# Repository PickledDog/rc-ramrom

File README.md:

# rc-ramrom
 Pageable RAM/ROM card for RC2014

## Overview
This RC2014-compatible board provides both ROM and RAM in a single card. ROM comes from an EPROM or EEPROM, with 8k/16k/32k granularity, and RAM is provided by a 128k x 8 SRAM. The ROM can be paged out and replaced by RAM.

## Memory details
For ROM, multiple EPROM and EEPROM chips are supported (8K through 64K from the 27Cxx and 28Cxx series - see below for supported chips). Room is provided for a ZIF socket for the EPROM, if desired. For RAM, an AS6C1008 SRAM is used, providing 128K of addressable memory. The upper 64K is difficult to use (page size is the entire 64K Z80 address space), but is there for the adventurous coder; consider this 64K of RAM for most purposes.

## Paging
The ROM is enabled by default, appearing at the bottom of memory (the RAM filling the rest of the address space). A config register allows it to be disabled (paged out) and replaced with RAM - this is required by systems like CP/M. A second config register selects between lower and upper 64K RAM banks. These registers are presented as two I/O devices to the system: ROM paging at 0x38, and RAM selection at 0x30. Writing a **1** to 0x38 disables the ROM, and writing a **1** to 0x30 switches to the upper RAM bank. Both of these actions are indicated by LEDs.

The ports are chosen to have the same organization as the [SC114 Motherboard](https://smallcomputercentral.wordpress.com/sc114-documentation/), and the ROM control address is common to most Z80 retrocomputers (the official RC2014 RAM/ROM cards included). As such, this board is basically the SC114's memory subsystem, in card form, with the addition of selectable page size and address.

## Chip support
The board supports 27C64, 27C128, 27C256, and 27C512 EPROMs, as well as 28C64 and 28C256 EEPROMs. Other chips with similar pinouts will *probably* work, but are untested. 150ns parts (like most 28C256s) are running at the edge of their specification in a standard 7.3Mhz system, and may require lowering the CPU clock. The [27C256](https://www.mouser.com/ProductDetail/AT27C256R-70PU/), [27C512](https://www.mouser.com/ProductDetail/AT27C512R-70PU/), and [28C256](https://www.mouser.com/ProductDetail/AT28C256-15PU/) can be purchased new.

## Firmware
Most (if not all) [RC2014 ROM images](https://github.com/RC2014Z80/RC2014/tree/master/ROMs) can be used unmodified (selecting the right images for your serial board, of course). Stephen C Cousins' excellent [Small Computer Monitor](https://smallcomputercentral.wordpress.com/small-computer-monitor/) can be used as well - all of the R\* configurations are supported. You will need an EPROM programmer (for example, a [TL866](https://www.ebay.com/sch/i.html?_nkw=tl866ii+plus)) to load the ROM images onto a chip.

## Jumper settings
Refer to the front and back of the board for detailed jumper setting instructions.

## Part selection
Bill Of Materials and part references are below. I recommend using gold-plated header for the bus connection - I use these ones from [Pololu](https://www.pololu.com/product/967) or [Sparkfun](https://www.sparkfun.com/products/553). A nice detail of these, is that they sit at the same height as double-row header in a backplane. The jumper headers can be snapped from regular (or double-row) breakaway header, for which eBay is substantially cheaper; the Mouser listings are provided for convenience.

The specified parts are just the ones I used, and can be substituted as needed - Mouser links provided for convenience and reference. A ZIF socket can be used for the EPROM - these are best [sourced from eBay](https://www.ebay.com/sch/i.html?_nkw=28+pin+zif+socket).

| Reference | Value | Qty | Mouser link |
| --------- | ----- | --- | ----------- |
| C1-C5 | 100nF ceramic | 5 | [KEMET C315C104M5U5TA](https://www.mouser.com/ProductDetail/C315C104M5U5TA7303) |
| D1, D2 | 3mm green LED | 2 | [Lite-On LTL-4231N](https://www.mouser.com/ProductDetail/LTL-4231N) |
| J1 | 1x40 right-angle header | 1 | [Wurth 61304011021](https://www.mouser.com/ProductDetail/61304011021) |
| JP1/2 | 2x3 header | 1 | [Amphenol 10129381-906002BLF](https://www.mouser.com/ProductDetail/10129381-906002BLF) |
| JP3/4/5 | 3x3 header | 1 | [Samtec TSW-103-07-L-T](https://www.mouser.com/ProductDetail/TSW-103-07-L-T) |
| JP6 | 2x2 header | 1 | [Amphenol 10129381-904002BLF](https://www.mouser.com/ProductDetail/10129381-904002BLF) |
| | jumpers | 7 | [Harwin M7583-46](https://www.mouser.com/ProductDetail/M7583-46)
| R1, R2 | 470Ω resistor | 2 | [Yageo CFR-25JT-52-470R](https://www.mouser.com/ProductDetail/CFR-25JT-52-470R) |
| R3, R4 | 10kΩ resistor | 2 | [Yageo CFR-25JT-52-10K](https://www.mouser.com/ProductDetail/CFR-25JT-52-10K) |
| U1 | EPROM | 1 | (see above for EPROM choices) |
| | socket | 1 | [Amphenol DILB28P-223TLF](https://www.mouser.com/ProductDetail/DILB28P-223TLF), or above ZIF |
| U2 | AS6C1008 SRAM | 1 | [Alliance AS6C1008-55PCN](https://www.mouser.com/ProductDetail/AS6C1008-55PCN) |
| | socket | 1 | [Amphenol DILB32P-223TLF](https://www.mouser.com/ProductDetail/DILB32P-223TLF) |
| U3 | 74HCT4075 | 1 | [TI CD74HCT4075E](https://www.mouser.com/ProductDetail/CD74HCT4075E) |
| U4 | 74HCT74 | 1 | [TI SN74HCT74N](https://www.mouser.com/ProductDetail/SN74HCT74N) |
| U5 | 74HCT138 | 1 | [TI SN74HCT138N](https://www.mouser.com/ProductDetail/SN74HCT138N) |

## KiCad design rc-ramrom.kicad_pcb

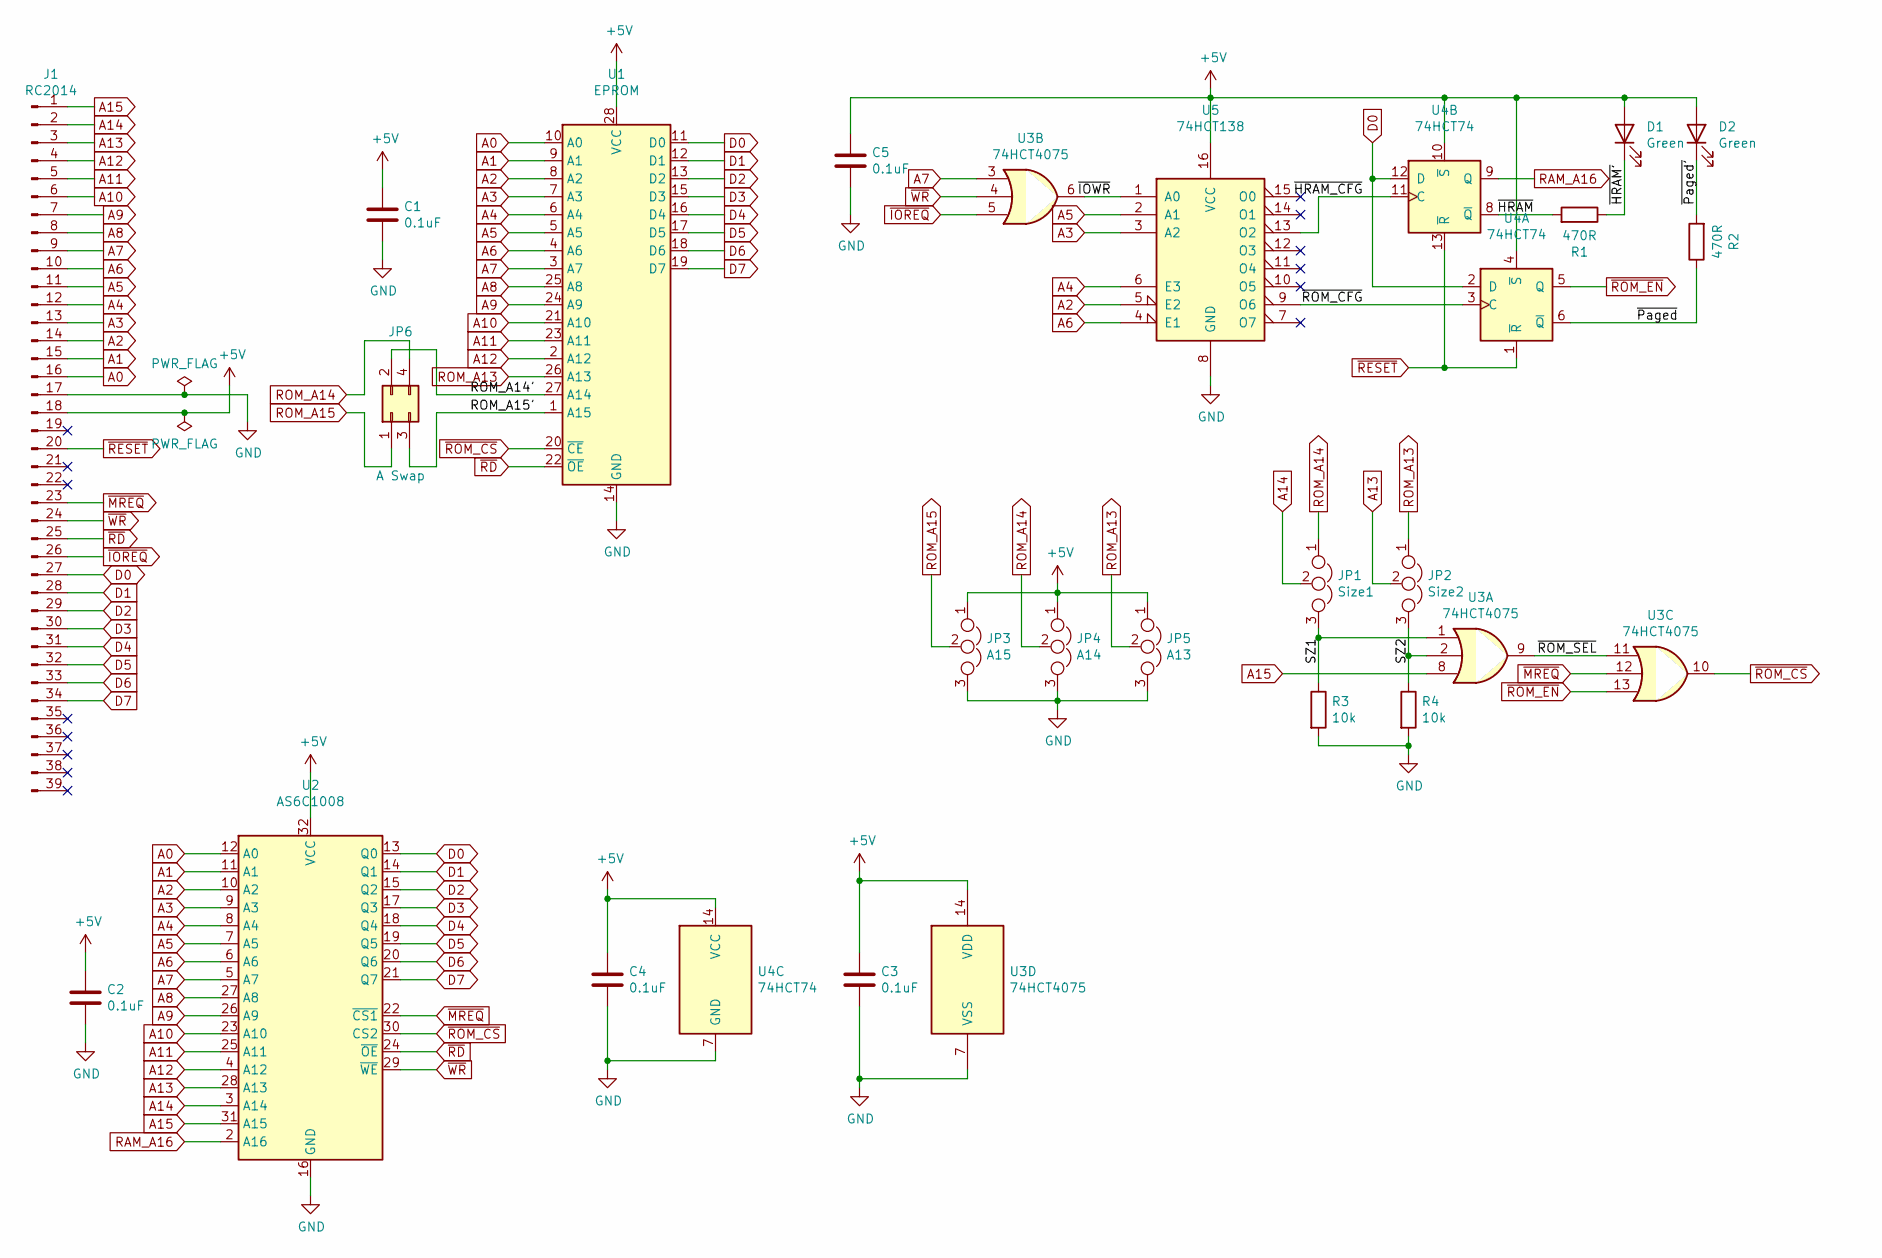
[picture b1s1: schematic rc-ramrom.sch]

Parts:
C1, C2, C3, C4, C5: 0.1uF; C_Disc_D3.0mm_W1.6mm_P2.50mm
D1, D2: Green; LED_D3.0mm
J1: RC2014; PinHeader_1x39_P2.54mm_Vertical
JP1: Size1; PinHeader_1x03_P2.54mm_Vertical
JP2: Size2; PinHeader_1x03_P2.54mm_Vertical
JP3: A15; PinHeader_1x03_P2.54mm_Vertical
JP4: A14; PinHeader_1x03_P2.54mm_Vertical
JP5: A13; PinHeader_1x03_P2.54mm_Vertical
JP6: A Swap; PinHeader_2x02_P2.54mm_Vertical
R1, R2: 470R; R_Axial_DIN0207_L6.3mm_D2.5mm_P7.62mm_Horizontal
R3, R4: 10k; R_Axial_DIN0207_L6.3mm_D2.5mm_P7.62mm_Horizontal
U1: EPROM; DIP-28_W15.24mm_Socket_LongPads
U2: AS6C1008; DIP-32_W15.24mm_LongPads
U3: 74HCT4075; DIP-14_W7.62mm_LongPads
U4: 74HCT74; DIP-14_W7.62mm_LongPads
U5: 74HCT138; DIP-16_W7.62mm_LongPads

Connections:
+5V: C1.1, C2.1, C3.1, C4.1, C5.1, D1.2 (A), D2.2 (A), J1.18, JP3.1, JP4.1, JP5.1, U1.28 (VCC), U2.32 (VCC), U3.14 (VDD), U4.4 (~S), U4.10 (~S), U4.14 (VCC), U5.16 (VCC)
/ROM_A14': JP6.2, U1.27 (A14)
/ROM_A15': JP6.3, U1.1 (A15)
/SZ1: JP1.3, R3.1, U3.1
/SZ2: JP2.3, R4.1, U3.2
/~HRAM: R1.2, U4.8 (~Q)
/~HRAM': D1.1 (K), R1.1
/~HRAM_CFG: U4.11 (C), U5.13 (O2)
/~IOWR: U3.6, U5.1 (A0)
/~Paged: R2.1, U4.6 (~Q)
/~Paged': D2.1 (K), R2.2
/~ROM_CFG: U4.3 (C), U5.9 (O6)
/~ROM_SEL: U3.9, U3.11
A0: J1.16, U1.10 (A0), U2.12 (A0)
A1: J1.15, U1.9 (A1), U2.11 (A1)
A2: J1.14, U1.8 (A2), U2.10 (A2), U5.5 (E2)
A3: J1.13, U1.7 (A3), U2.9 (A3), U5.3 (A2)
A4: J1.12, U1.6 (A4), U2.8 (A4), U5.6 (E3)
A5: J1.11, U1.5 (A5), U2.7 (A5), U5.2 (A1)
A6: J1.10, U1.4 (A6), U2.6 (A6), U5.4 (E1)
A7: J1.9, U1.3 (A7), U2.5 (A7), U3.3
A8: J1.8, U1.25 (A8), U2.27 (A8)
A9: J1.7, U1.24 (A9), U2.26 (A9)
A10: J1.6, U1.21 (A10), U2.23 (A10)
A11: J1.5, U1.23 (A11), U2.25 (A11)
A12: J1.4, U1.2 (A12), U2.4 (A12)
A13: J1.3, JP2.2, U2.28 (A13)
A14: J1.2, JP1.2, U2.3 (A14)
A15: J1.1, U2.31 (A15), U3.8
D0: J1.27, U1.11 (D0), U2.13 (Q0), U4.2 (D), U4.12 (D)
D1: J1.28, U1.12 (D1), U2.14 (Q1)
D2: J1.29, U1.13 (D2), U2.15 (Q2)
D3: J1.30, U1.15 (D3), U2.17 (Q3)
D4: J1.31, U1.16 (D4), U2.18 (Q4)
D5: J1.32, U1.17 (D5), U2.19 (Q5)
D6: J1.33, U1.18 (D6), U2.20 (Q6)
D7: J1.34, U1.19 (D7), U2.21 (Q7)
GND: C1.2, C2.2, C3.2, C4.2, C5.2, J1.17, JP3.3, JP4.3, JP5.3, R3.2, R4.2, U1.14 (GND), U2.16 (GND), U3.7 (VSS), U4.7 (GND), U5.8 (GND)
RAM_A16: U2.2 (A16), U4.9 (Q)
ROM_A13: JP2.1, JP5.2, U1.26 (A13)
ROM_A14: JP1.1, JP4.2, JP6.4
ROM_A15: JP3.2, JP6.1
~IOREQ: J1.26, U3.5
~MREQ: J1.23, U2.22 (~CS1), U3.12
~RD: J1.25, U1.22 (~OE), U2.24 (~OE)
~RESET: J1.20, U4.1 (~R), U4.13 (~R)
~ROM_CS: U1.20 (~CE), U2.30 (CS2), U3.10
~ROM_EN: U3.13, U4.5 (Q)
~WR: J1.24, U2.29 (~WE), U3.4

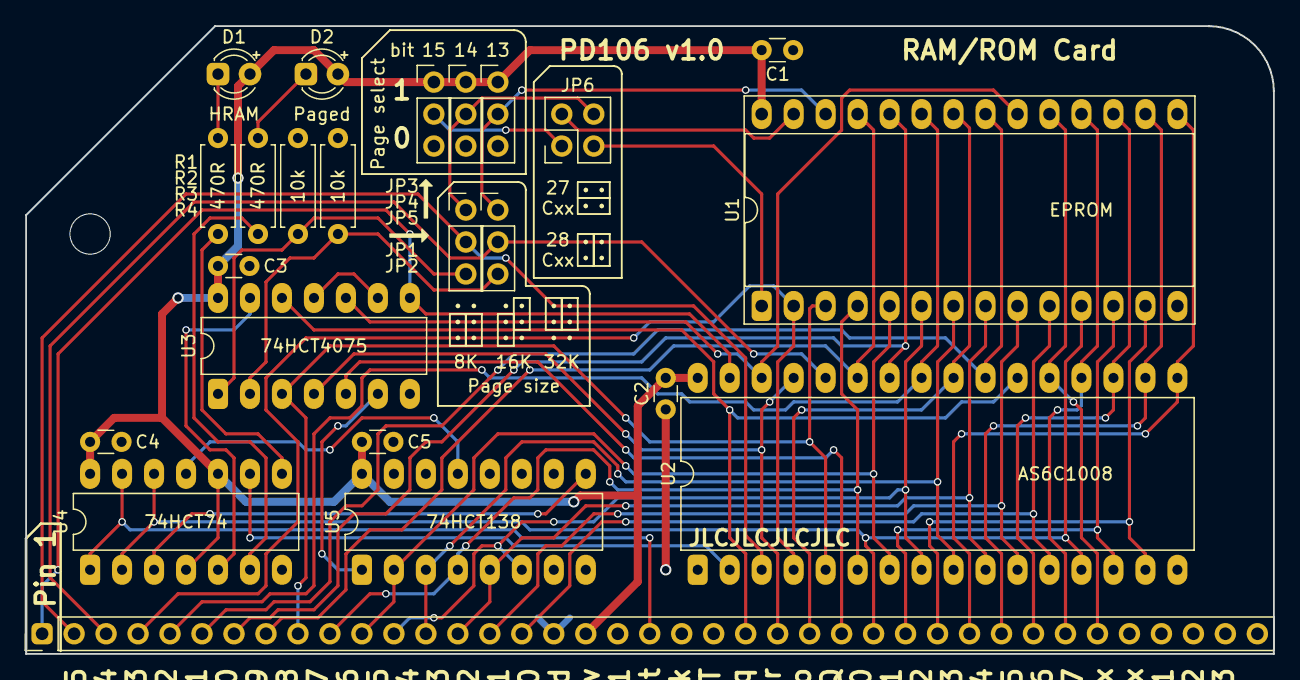
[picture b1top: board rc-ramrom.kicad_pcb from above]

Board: 2 copper layers, 99.1 x 49.9 mm, 23 parts (0 on the bottom side), 49 nets.

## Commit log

2021-01-02 Initial commit of rc-ramrom/PD106
2021-01-05 Neatened routing
2021-01-24 Added README
2021-02-10 Updated silk, moved to v1.0
